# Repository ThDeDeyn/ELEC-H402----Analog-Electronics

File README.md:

# ELEC-H402----Analog-Electronics
 Files made for the labs

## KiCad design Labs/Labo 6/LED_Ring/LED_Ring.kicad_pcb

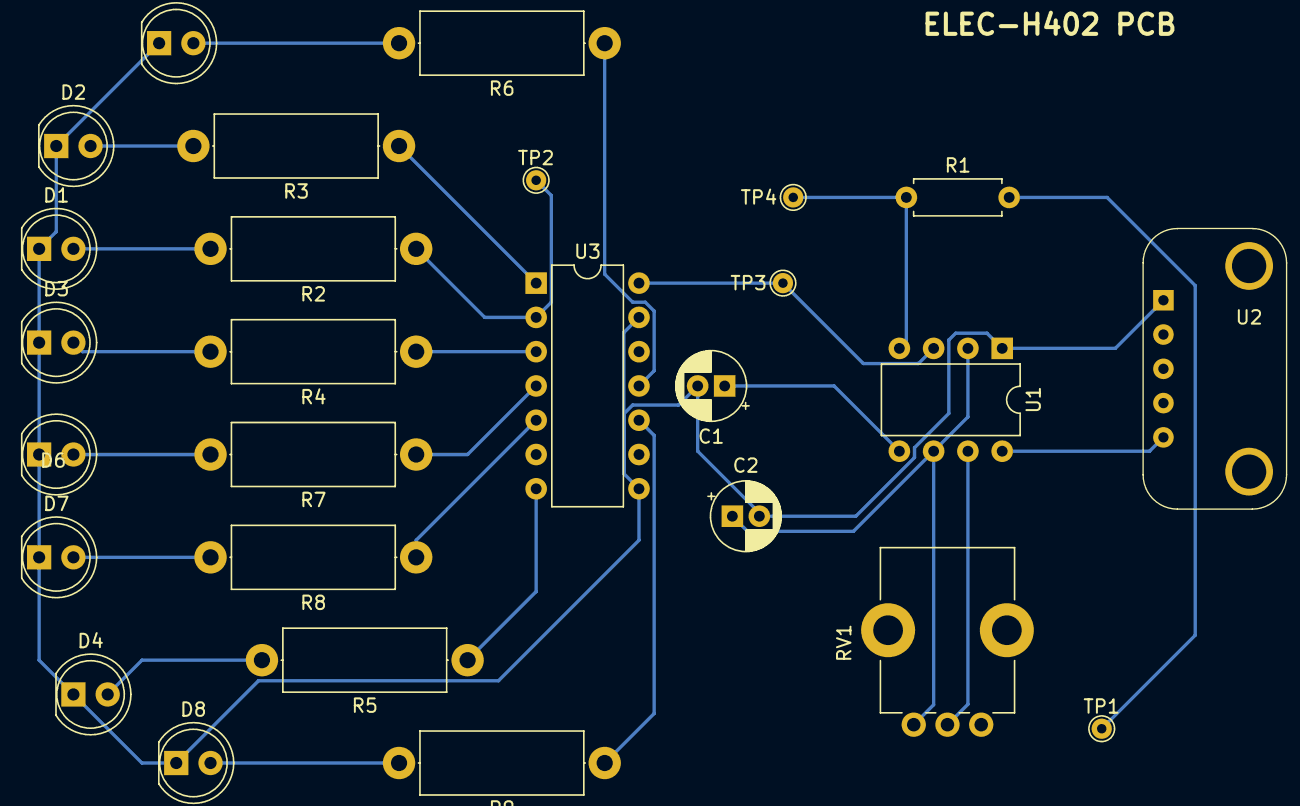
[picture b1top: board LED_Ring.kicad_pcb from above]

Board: 2 copper layers, 27 parts (0 on the bottom side), 24 nets.

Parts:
C1: 1uF; CP_Radial_D5.0mm_P2.00mm
C2: 220nF; CP_Radial_D5.0mm_P2.00mm
D1, D2, D3, D4, D5, D6, D7, D8: LED; LED_D5.0mm
R1: 100k; R_Axial_DIN0207_L6.3mm_D2.5mm_P7.62mm_Horizontal
R2, R3, R4, R5, R6, R7, R8, R9: 100; R_Axial_DIN0414_L11.9mm_D4.5mm_P15.24mm_Horizontal
RV1: 100k; Potentiometer_Bourns_PTV09A-1_Single_Vertical
TP1, TP2, TP3, TP4: TestPoint; TestPoint_THTPad_D1.5mm_Drill0.7mm
U1: NE555P; DIP-8_W7.62mm
U2: micro-b; micro-b_adafruit
U3: CD4022BE; DIP-14_W7.62mm

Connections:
+5V: U1.8 (VCC), U2.5 (5V)
GND: C1.2, C2.2, D1.1 (K), D2.1 (K), D3.1 (K), D4.1 (K), D5.1 (K), D6.1 (K), D7.1 (K), D8.1 (K), U1.1 (GND), U2.1 (GND), U3.8 (VSS), U3.13 (CLK_inhib)
unnamed: D1.2 (A), R2.2
unnamed: D2.2 (A), R3.2
unnamed: D3.2 (A), R4.2
unnamed: D4.2 (A), R5.2
unnamed: D5.2 (A), R6.2
unnamed: D6.2 (A), R7.2
unnamed: D7.2 (A), R8.2
unnamed: D8.2 (A), R9.2
unnamed: R1.2, RV1.1, TP1.1
unnamed: R3.1, U3.1
unnamed: C1.1, U1.5 (CV)
unnamed: RV1.2, U1.7 (DIS)
unnamed: TP3.1, U1.3 (Q), U3.14 (CLK)
unnamed: R1.1, TP4.1, U1.4 (R)
unnamed: C2.1, RV1.3, U1.2 (TR), U1.6 (THR)
unnamed: R2.1, TP2.1, U3.2 (0)
unnamed: R4.1, U3.3 (2)
unnamed: R5.1, U3.7 (3)
unnamed: R6.1, U3.11 (4)
unnamed: R7.1, U3.4 (5)
unnamed: R8.1, U3.5 (6)
unnamed: R9.1, U3.10 (7)

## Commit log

2023-05-22 Notes added
